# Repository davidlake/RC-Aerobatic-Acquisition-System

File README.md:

# RC-Aerobatic-Acquisition-System
System to determine orientation and position of aerobatic RC models

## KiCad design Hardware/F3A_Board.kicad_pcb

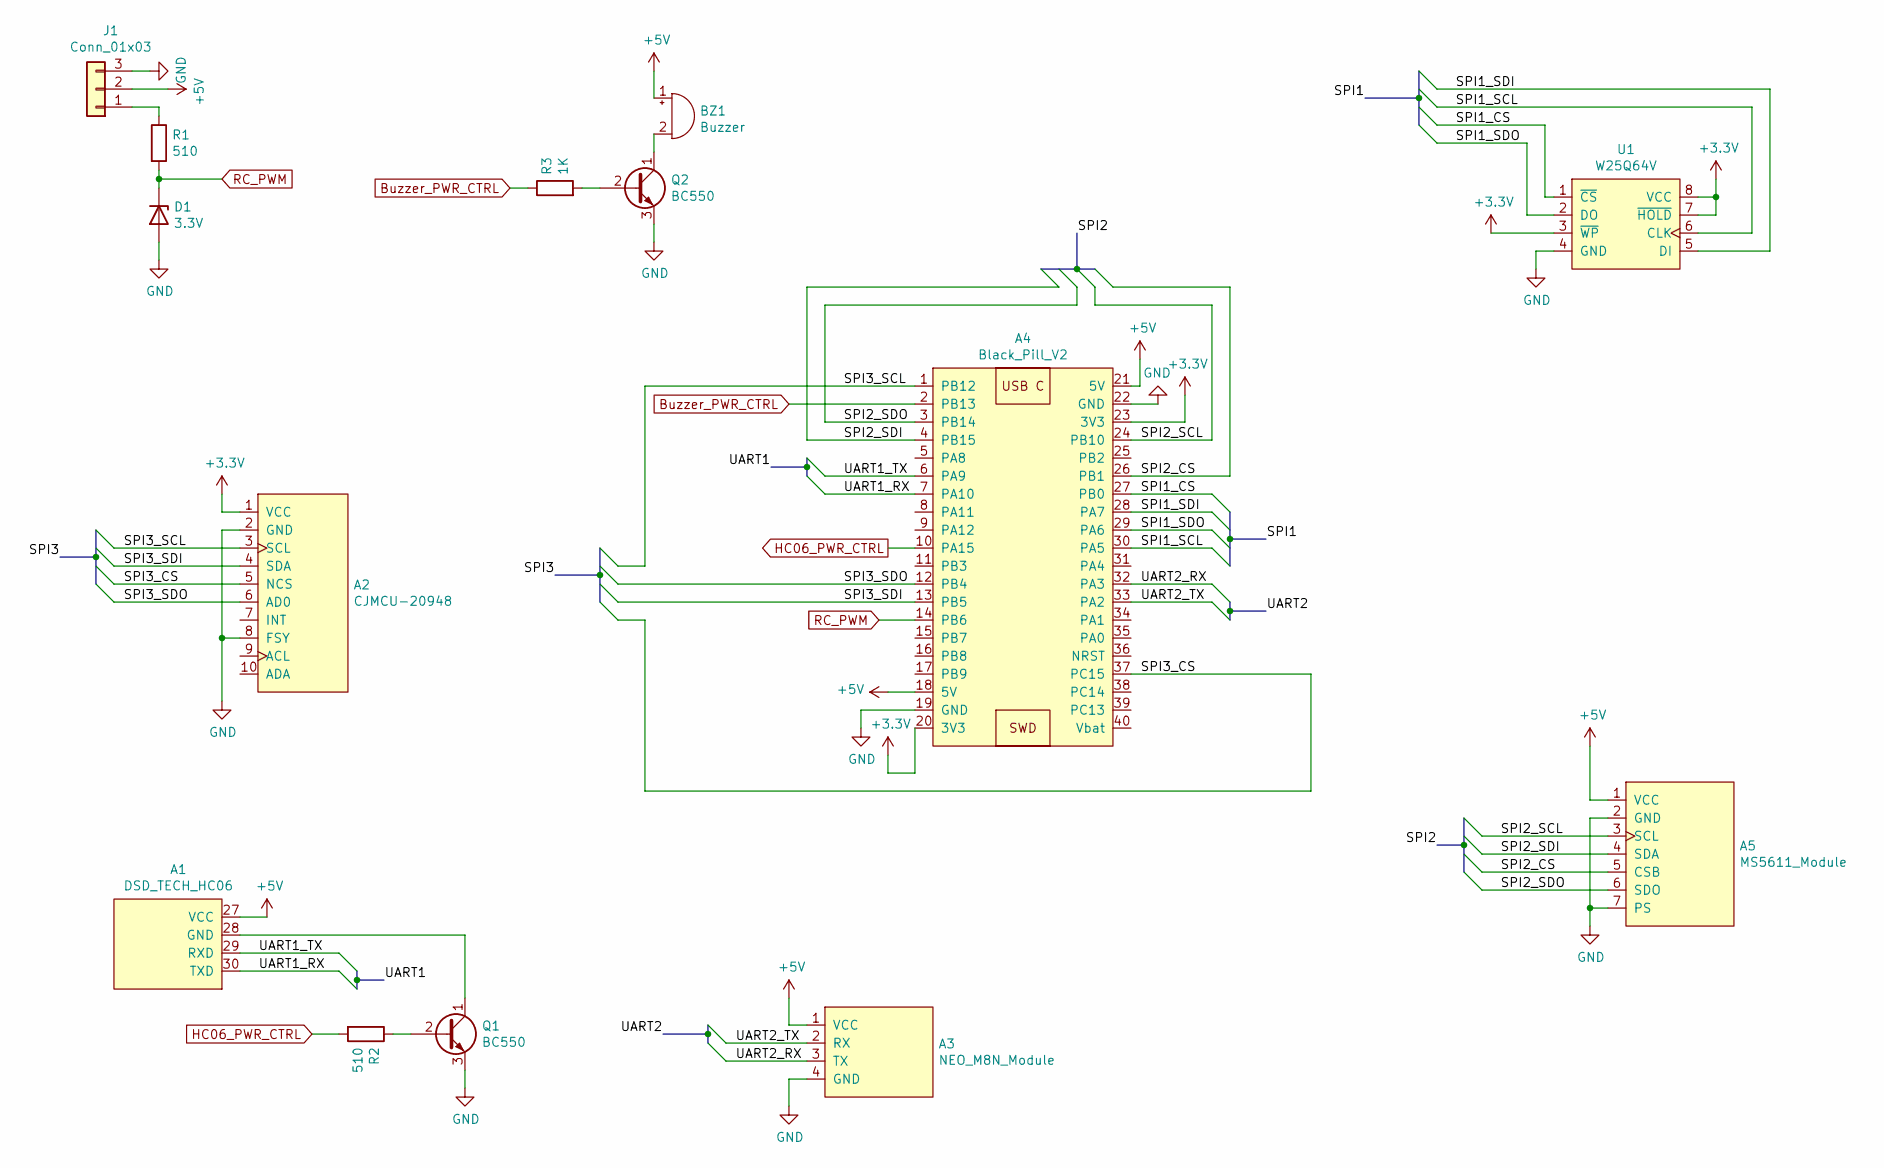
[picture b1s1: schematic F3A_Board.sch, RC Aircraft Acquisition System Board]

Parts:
A1: DSD_TECH_HC06
A2: CJMCU-20948; CJMCU_20948
A3: NEO_M8N_Module
A4: Black_Pill_V2
A5: MS5611_Module
BZ1: Buzzer; Buzzer_12x9.5RM7.6
D1: 3.3V; D_DO-35_SOD27_P7.62mm_Horizontal
J1: Conn_01x03; JST_XH_S3B-XH-A-1_1x03_P2.50mm_Horizontal
Q1, Q2: BC550; TO-92S_Wide
R1, R2: 510; R_Axial_DIN0204_L3.6mm_D1.6mm_P7.62mm_Horizontal
R3: 1K; R_Axial_DIN0204_L3.6mm_D1.6mm_P7.62mm_Horizontal
U1: W25Q64V; DIP-8_W7.62mm

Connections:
+3V3: A2.1 (VCC), A4.20 (3V3), A4.23 (3V3), U1.3 (~WP), U1.7 (~HOLD), U1.8 (VCC)
+5V: A1.27 (VCC), A3.1 (VCC), A4.18 (5V), A4.21 (5V), A5.1 (VCC), BZ1.1 (-), J1.2
/SPI1_CS: A4.27 (PB0), U1.1 (~CS)
/SPI1_SCL: A4.30 (PA5), U1.6 (CLK)
/SPI1_SDI: A4.28 (PA7), U1.5 (DI)
/SPI1_SDO: A4.29 (PA6), U1.2 (DO)
/SPI2_CS: A4.26 (PB1), A5.5 (CSB)
/SPI2_SCL: A4.24 (PB10), A5.3 (SCL)
/SPI2_SDI: A4.4 (PB15), A5.4 (SDA)
/SPI2_SDO: A4.3 (PB14), A5.6 (SDO)
/SPI3_CS: A2.5 (NCS), A4.37 (PC15)
/SPI3_SCL: A2.3 (SCL), A4.1 (PB12)
/SPI3_SDI: A2.4 (SDA), A4.13 (PB5)
/SPI3_SDO: A2.6 (AD0), A4.12 (PB4)
/UART1_RX: A1.30 (TXD), A4.7 (PA10)
/UART1_TX: A1.29 (RXD), A4.6 (PA9)
/UART2_RX: A3.3 (TX), A4.32 (PA3)
/UART2_TX: A3.2 (RX), A4.33 (PA2)
Buzzer_PWR_CTRL: A4.2 (PB13), R3.1
GND: A2.2 (GND), A2.8 (FSY), A3.4 (GND), A4.19 (GND), A4.22 (GND), A5.2 (GND), A5.7 (PS), D1.2 (A), J1.3, Q1.3 (E), Q2.3 (E), U1.4 (GND)
HC06_PWR_CTRL: A4.10 (PA15), R2.2
unnamed: A1.28 (GND), Q1.1 (C)
unnamed: BZ1.2 (+), Q2.1 (C)
unnamed: J1.1, R1.1
unnamed: Q1.2 (B), R2.1
unnamed: Q2.2 (B), R3.2
RC_PWM: A4.14 (PB6), D1.1 (K), R1.2

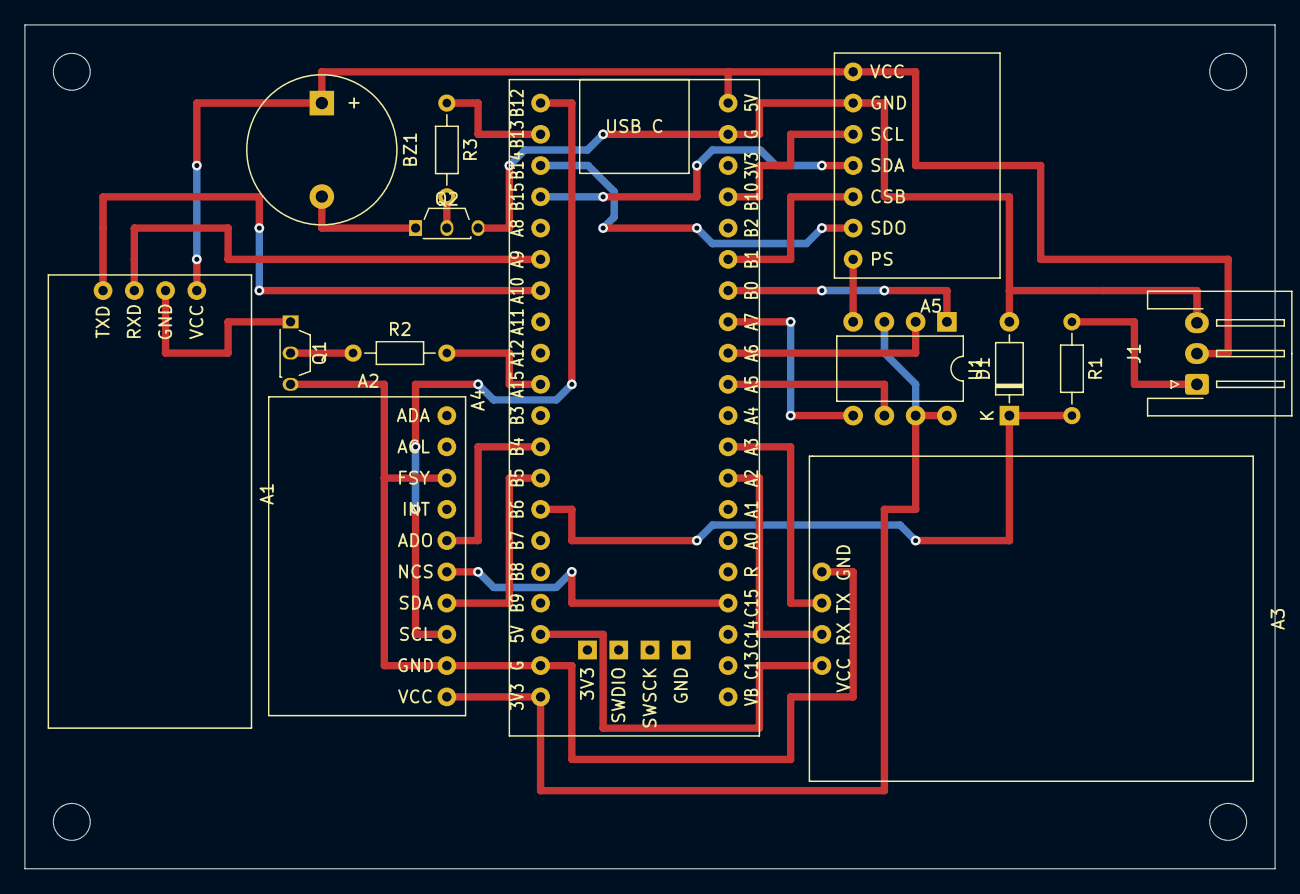
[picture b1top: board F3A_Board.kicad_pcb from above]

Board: 2 copper layers, 101.6 x 68.6 mm, 14 parts (0 on the bottom side), 27 nets.

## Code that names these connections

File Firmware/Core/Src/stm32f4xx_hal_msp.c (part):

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
    __HAL_RCC_GPIOA_CLK_ENABLE();
    /**SPI1 GPIO Configuration
    PA5     ------> SPI1_SCK
    PA6     ------> SPI1_MISO
    PA7     ------> SPI1_MOSI
    */
    GPIO_InitStruct.Pin = W25Q64_SPI1_SCK_Pin|W25Q64_SPI1_MISO_Pin|W25Q64_SPI1_MOSI_Pin;
    GPIO_InitStruct.Mode = GPIO_MODE_AF_PP;
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
    __HAL_RCC_GPIOB_CLK_ENABLE();
    /**SPI2 GPIO Configuration
    PB10     ------> SPI2_SCK
    PB14     ------> SPI2_MISO
    PB15     ------> SPI2_MOSI
    */
    GPIO_InitStruct.Pin = MS5611_SPI2_SCK_Pin|MS5611_SPI2_MISO_Pin|MS5611_SPI2_MOSI_Pin;
    GPIO_InitStruct.Mode = GPIO_MODE_AF_PP;
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
    __HAL_RCC_GPIOB_CLK_ENABLE();
    /**SPI3 GPIO Configuration
    PB12     ------> SPI3_SCK
    PB4     ------> SPI3_MISO
    PB5     ------> SPI3_MOSI
    */
    GPIO_InitStruct.Pin = ICM20948_SPI3_SCK_Pin;
    GPIO_InitStruct.Mode = GPIO_MODE_AF_PP;
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    __HAL_RCC_SPI1_CLK_DISABLE();

    /**SPI1 GPIO Configuration
    PA5     ------> SPI1_SCK
    PA6     ------> SPI1_MISO
    PA7     ------> SPI1_MOSI
    */
    HAL_GPIO_DeInit(GPIOA, W25Q64_SPI1_SCK_Pin|W25Q64_SPI1_MISO_Pin|W25Q64_SPI1_MOSI_Pin);

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    __HAL_RCC_SPI2_CLK_DISABLE();

    /**SPI2 GPIO Configuration
    PB10     ------> SPI2_SCK
    PB14     ------> SPI2_MISO
    PB15     ------> SPI2_MOSI
    */
    HAL_GPIO_DeInit(GPIOB, MS5611_SPI2_SCK_Pin|MS5611_SPI2_MISO_Pin|MS5611_SPI2_MOSI_Pin);

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    __HAL_RCC_SPI3_CLK_DISABLE();

    /**SPI3 GPIO Configuration
    PB12     ------> SPI3_SCK
    PB4     ------> SPI3_MISO
    PB5     ------> SPI3_MOSI
    */
    HAL_GPIO_DeInit(GPIOB, ICM20948_SPI3_SCK_Pin|ICM20948_SPI3_MISO_Pin|ICM20948_SPI3_MOSI_Pin);

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
    __HAL_RCC_GPIOB_CLK_ENABLE();
    /**TIM4 GPIO Configuration
    PB6     ------> TIM4_CH1
    */
    GPIO_InitStruct.Pin = RC_PWM_TIM4_CH1_Pin;
    GPIO_InitStruct.Mode = GPIO_MODE_AF_PP;
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    __HAL_RCC_TIM4_CLK_DISABLE();

    /**TIM4 GPIO Configuration
    PB6     ------> TIM4_CH1
    */
    HAL_GPIO_DeInit(RC_PWM_TIM4_CH1_GPIO_Port, RC_PWM_TIM4_CH1_Pin);

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
    __HAL_RCC_GPIOA_CLK_ENABLE();
    /**USART1 GPIO Configuration
    PA9     ------> USART1_TX
    PA10     ------> USART1_RX
    */
    GPIO_InitStruct.Pin = HC06_USART1_TX_Pin|HC06_USART1_RX_Pin;
    GPIO_InitStruct.Mode = GPIO_MODE_AF_PP;
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
    __HAL_RCC_GPIOA_CLK_ENABLE();
    /**USART2 GPIO Configuration
    PA2     ------> USART2_TX
    PA3     ------> USART2_RX
    */
    GPIO_InitStruct.Pin = UBLOX_USART2_TX_Pin|UBLOX_USART2_RX_Pin;
    GPIO_InitStruct.Mode = GPIO_MODE_AF_PP;
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    __HAL_RCC_USART1_CLK_DISABLE();

    /**USART1 GPIO Configuration
    PA9     ------> USART1_TX
    PA10     ------> USART1_RX
    */
    HAL_GPIO_DeInit(GPIOA, HC06_USART1_TX_Pin|HC06_USART1_RX_Pin);

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    __HAL_RCC_USART2_CLK_DISABLE();

    /**USART2 GPIO Configuration
    PA2     ------> USART2_TX
    PA3     ------> USART2_RX
    */
    HAL_GPIO_DeInit(GPIOA, UBLOX_USART2_TX_Pin|UBLOX_USART2_RX_Pin);

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
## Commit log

2021-08-16 Creation commit
2021-08-16 Eliminate HC06 baudrate config line
2021-08-17 Change F3ASystem folder name by Firmware name
2021-08-17 Adding components datasheet folder
2021-08-18 Renaming datasheets folders
2021-08-18 Change folder name
2021-08-18 Adding schematic folder
2021-08-21 Adding schematics folders
2021-08-21 Eliminate PDF
2021-08-21 Add datasheet
2021-08-22 Adding KiCad board design folder and files
2021-08-23 Adding Zener datasheets
2021-08-23 Changing pins names
2021-08-23 Changing pin labels
2021-08-24 Changes: SPI1 preescaler from 2 to 4. Changes in the hardware plot
2021-08-24 Nothing
2021-08-25 Tried power consumption tool
2021-08-25 Not enabling uartidle in ublox init function
2021-08-25 Now uart for HC06 just works with regular interrupts (no idle line)
2021-08-26 Adding 3 test pins
2021-08-26 PCBnew updated Created step file
2021-08-26 Adding arduino file to simulate PWM from receiver
2021-08-26 Changing description
2021-08-27 Adding assembly drawing and 3D assembly
2021-08-27 Small change
2021-08-27 Not important
2021-08-28 Adding Matlab application files
2021-08-28 Prueba
2021-08-28 Adding plastic screws docu and links
2021-08-28 Changing things in sumulation of trajectories and sensores
2021-08-31 Simulation work
2021-08-31 Adding component steps and drawings
2021-08-31 Update drawings with SLA material (epoxy resin) and xy direciton mark on the cap
2021-09-01 Improvements on the main application and addition of plane model
2021-09-01 Adding flight tracks manager to store coordinates
2021-09-01 Adding simulated sensor file to make trials
2021-09-01 Trying things with the stl representation with patches...
2021-09-01 Updated app
2021-09-04 Change UART HC06 to higher baudrate 921600
2021-09-04 Increase delay time for bluetooth transmission
2021-09-04 Add information about already received packets to progress bar
2021-09-04 Pruebas
2021-09-09 Adding comments
2021-09-09 Adding PNP transistor documentation
2021-09-09 App mods
2021-09-09 HC06 now controlled with high side switch
2021-09-09 Adding spice simulation for HC06 high side switch
2021-09-10 Change readme

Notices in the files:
Firmware/Core/Src/stm32f4xx_hal_msp.c:
© Copyright (c) 2020 STMicroelectronics.
All rights reserved.
This software component is licensed by ST under BSD 3-Clause license,
the "License"; You may not use this file except in compliance with the
License. You may obtain a copy of the License at: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
(C) COPYRIGHT STMicroelectronics *****END OF FILE
